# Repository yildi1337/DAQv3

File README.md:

# DAQv3
A Dual-Channel, Low Noise, Modular, 100 kHz Bandwidth, 24-Bit Data Acquisition (DAQ) Device / FFT Signal Analyzer

# Table of Contents

- **[Introduction](#introduction)**
- **[CAD Model](#cad-model)**
- **[Modules](#modules)**
  - [AnalogConversion_v1](#AnalogConversion_v1)
  - [AnalogConversion_v2](#AnalogConversion_v2)
  - [AnalogConversion_v3](#AnalogConversion_v3)
  - [Backplane_v1](#Backplane_v1)
  - [DigitalBackend_v1](#DigitalBackend_v1)
  - [PowerSupply_5V_v1](#PowerSupply_5V_v1)
  - [PowerSupply_5V_v2](#PowerSupply_5V_v2)
  - [PowerSupply_12V_v1](#PowerSupply_12V_v1)
  - [PowerSupply_12V_v2](#PowerSupply_12V_v2)
  - [USBConnectors_v1](#USBConnectors_v1)
- **[Firmware](#firmware)**
- **[USB Driver](#usb-driver)**
- **[Debug and Control Interface](#debug-and-control-interface)**
- **[Measurement Results](#measurement-results)**
  - [Linear Power Supply vs. Switched-Mode Power Supply](#linear-power-supply-vs-switched-mode-power-supply)
  - [Differential Input Module (AnalogConversion_v3)](#differential-input-module-analogconversion_v3)

# Introduction

Work in progress ...

# Rack
+ [Card Rail](https://it.rs-online.com/web/p/montanti-rack/2457848)
+ [Front Pannel Large](https://it.rs-online.com/web/p/accessori-per-contenitori/2879769) (10 HP)
+ [Front Pannel Small](https://us.rs-online.com/product/nvent-schroff/20848664/70294016/)  (4 HP)
+ [Case](https://it.rs-online.com/web/p/contenitori-e-scatole-rack/2550700?searchId=d65bfb2c-882b-444f-99ba-9c0d112e01d9&gb=s)  (42 HP)
+ [IEC Connector](https://it.rs-online.com/web/p/filtri-iec/8703669)

# CAD Model

The complete CAD model can be downloaded <a href="https://github.com/yildi1337/DAQv3/tree/main/cad_complete/inventor">here</a> (Autodesk Inventor 2023 files) including all <a href="#modules">modules</a> and the case.

# Modules

## AnalogConversion_v1

- [Schematics (PDF)](https://github.com/yildi1337/DAQv3/blob/main/schematics/AnalogConversion_v1_Schematics.pdf)
- [Schematics (Eagle)](https://github.com/yildi1337/DAQv3/blob/main/eagle/AnalogConversion_v1.sch)
- [Board (Eagle)](https://github.com/yildi1337/DAQv3/blob/main/eagle/AnalogConversion_v1.brd)
- [Gerber Files](https://github.com/yildi1337/DAQv3/blob/main/pcb_gerber/AnalogConversion_v1_2022-03-20.zip)
- [3D Step File](https://github.com/yildi1337/DAQv3/blob/main/cad_modules_step/AnalogConversion_v1.step)
- [Bill of Materials](https://github.com/yildi1337/DAQv3/blob/main/pcb_bom/BOM_AnalogConversion_v1.txt)

## AnalogConversion_v2

- [Schematics (PDF)](https://github.com/yildi1337/DAQv3/blob/main/schematics/AnalogConversion_v2_Schematics.pdf)
- [Schematics (Eagle)](https://github.com/yildi1337/DAQv3/blob/main/eagle/AnalogConversion_v2.sch)
- [Board (Eagle)](https://github.com/yildi1337/DAQv3/blob/main/eagle/AnalogConversion_v2.brd)
- [Gerber Files](https://github.com/yildi1337/DAQv3/blob/main/pcb_gerber/AnalogConversion_v2_2022-05-25.zip)
- [3D Step File](https://github.com/yildi1337/DAQv3/blob/main/cad_modules_step/AnalogConversion_v2.step)
- [Bill of Materials](https://github.com/yildi1337/DAQv3/blob/main/pcb_bom/BOM_AnalogConversion_v2.txt)

## AnalogConversion_v3

- [Schematics (PDF)](https://github.com/yildi1337/DAQv3/blob/main/schematics/AnalogConversion_v3_Schematics.pdf)
- [Schematics (Eagle)](https://github.com/yildi1337/DAQv3/blob/main/eagle/AnalogConversion_v3.sch)
- [Board (Eagle)](https://github.com/yildi1337/DAQv3/blob/main/eagle/AnalogConversion_v3.brd)
- [Gerber Files](https://github.com/yildi1337/DAQv3/blob/main/pcb_gerber/AnalogConversion_v3_2022-07-25.zip)
- [3D Step File](https://github.com/yildi1337/DAQv3/blob/main/cad_modules_step/AnalogConversion_v3.step)
- [Bill of Materials](https://github.com/yildi1337/DAQv3/blob/main/pcb_bom/BOM_AnalogConversion_v3.txt)

## Backplane_v1

- [Schematics (PDF)](https://github.com/yildi1337/DAQv3/blob/main/schematics/Backplane_v1_Schematics.pdf)
- [Schematics (Eagle)](https://github.com/yildi1337/DAQv3/blob/main/eagle/Backplane_v1.sch)
- [Board (Eagle)](https://github.com/yildi1337/DAQv3/blob/main/eagle/Backplane_v1.brd)
- [Gerber Files](https://github.com/yildi1337/DAQv3/blob/main/pcb_gerber/Backplane_v1_2022-03-20.zip)
- [3D Step File](https://github.com/yildi1337/DAQv3/blob/main/cad_modules_step/Backplane_v1.step)
- [Bill of Materials](https://github.com/yildi1337/DAQv3/blob/main/pcb_bom/BOM_Backplane_v1.txt)

## DigitalBackend_v1

- [Schematics (PDF)](https://github.com/yildi1337/DAQv3/blob/main/schematics/DigitalBackend_v1_Schematics.pdf)
- [Schematics (Eagle)](https://github.com/yildi1337/DAQv3/blob/main/eagle/DigitalBackend_v1.sch)
- [Board (Eagle)](https://github.com/yildi1337/DAQv3/blob/main/eagle/DigitalBackend_v1.brd)
- [Gerber Files](https://github.com/yildi1337/DAQv3/blob/main/pcb_gerber/DigitalBackend_v1_2022-03-20.zip)
- [3D Step File](https://github.com/yildi1337/DAQv3/blob/main/cad_modules_step/DigitalBackend_v1.step)
- [Bill of Materials](https://github.com/yildi1337/DAQv3/blob/main/pcb_bom/BOM_DigitalBackend_v1.txt)

## PowerSupply_12V_v1

- [Schematics (PDF)](https://github.com/yildi1337/DAQv3/blob/main/schematics/PowerSupply_12V_v1_Schematics.pdf)
- [Schematics (Eagle)](https://github.com/yildi1337/DAQv3/blob/main/eagle/PowerSupply_12V_v1.sch)
- [Board (Eagle)](https://github.com/yildi1337/DAQv3/blob/main/eagle/PowerSupply_12V_v1.brd)
- [Gerber Files](https://github.com/yildi1337/DAQv3/blob/main/pcb_gerber/PowerSupply_12V_v1_2022-03-20.zip)
- [3D Step File](https://github.com/yildi1337/DAQv3/blob/main/cad_modules_step/PowerSupply_12V_v1.step)
- [Bill of Materials](https://github.com/yildi1337/DAQv3/blob/main/pcb_bom/BOM_PowerSupply_12V_v1.txt)

## PowerSupply_12V_v2

- [Schematics (PDF)](https://github.com/yildi1337/DAQv3/blob/main/schematics/PowerSupply_12V_v2_Schematics.pdf)
- [Schematics (Eagle)](https://github.com/yildi1337/DAQv3/blob/main/eagle/PowerSupply_12V_v2.sch)
- [Board (Eagle)](https://github.com/yildi1337/DAQv3/blob/main/eagle/PowerSupply_12V_v2.brd)
- [Gerber Files](https://github.com/yildi1337/DAQv3/blob/main/pcb_gerber/PowerSupply_12V_v2_2022-05-25.zip)
- [3D Step File](https://github.com/yildi1337/DAQv3/blob/main/cad_modules_step/PowerSupply_12V_v2.step)
- [Bill of Materials](https://github.com/yildi1337/DAQv3/blob/main/pcb_bom/BOM_PowerSupply_12V_v2.txt)

## PowerSupply_5V_v1

- [Schematics (PDF)](https://github.com/yildi1337/DAQv3/blob/main/schematics/PowerSupply_5V_v1_Schematics.pdf)
- [Schematics (Eagle)](https://github.com/yildi1337/DAQv3/blob/main/eagle/PowerSupply_5V_v1.sch)
- [Board (Eagle)](https://github.com/yildi1337/DAQv3/blob/main/eagle/PowerSupply_5V_v1.brd)
- [Gerber Files](https://github.com/yildi1337/DAQv3/blob/main/pcb_gerber/PowerSupply_5V_v1_2022-03-20.zip)
- [3D Step File](https://github.com/yildi1337/DAQv3/blob/main/cad_modules_step/PowerSupply_5V_v1.step)
- [Bill of Materials](https://github.com/yildi1337/DAQv3/blob/main/pcb_bom/BOM_PowerSupply_5V_v1.txt)

## PowerSupply_5V_v2

- [Schematics (PDF)](https://github.com/yildi1337/DAQv3/blob/main/schematics/PowerSupply_5V_v2_Schematics.pdf)
- [Schematics (Eagle)](https://github.com/yildi1337/DAQv3/blob/main/eagle/PowerSupply_5V_v2.sch)
- [Board (Eagle)](https://github.com/yildi1337/DAQv3/blob/main/eagle/PowerSupply_5V_v2.brd)
- [Gerber Files](https://github.com/yildi1337/DAQv3/blob/main/pcb_gerber/PowerSupply_5V_v2_2022-05-25.zip)
- [3D Step File](https://github.com/yildi1337/DAQv3/blob/main/cad_modules_step/PowerSupply_5V_v2.step)
- [Bill of Materials](https://github.com/yildi1337/DAQv3/blob/main/pcb_bom/BOM_PowerSupply_5V_v2.txt)

## USBConnectors_v1

- [Schematics (PDF)](https://github.com/yildi1337/DAQv3/blob/main/schematics/USBConnectors_v1_Schematics.pdf)
- [Schematics (Eagle)](https://github.com/yildi1337/DAQv3/blob/main/eagle/USBConnectors_v1.sch)
- [Board (Eagle)](https://github.com/yildi1337/DAQv3/blob/main/eagle/USBConnectors_v1.brd)
- [Gerber Files](https://github.com/yildi1337/DAQv3/blob/main/pcb_gerber/USBConnectors_v1_2022-03-14.zip)
- [3D Step File](https://github.com/yildi1337/DAQv3/blob/main/cad_modules_step/USBConnectors_v1.step)
- [Bill of Materials](https://github.com/yildi1337/DAQv3/blob/main/pcb_bom/BOM_USBConnectors_v1.txt)

# Firmware

The firmware running on the STM32H753ZIT6 is mainly written in ANSI C and has been developed in <a href="https://www.st.com/en/development-tools/stm32cubeide.html">STM32CubeIDE</a> version 1.10.1 utilizing the official <a href="https://github.com/STMicroelectronics/stm32h7xx_hal_driver">STM32H7xx_HAL_Driver</a>. Among others, the firmware performs the following tasks:

- Configuration of the ADC AD7768 (on module <a href="#AnalogConversion_v3">AnalogConversion_v3</a>) via SPI (SPI_3).
- Reception of sampled data from the ADC AD7768 via SPI (SPI_2) and DMA (DMA1_Stream0).
- Transmission of sampled data from the ADC AD7768 via USB 2.0 Hi-Speed to the PC utilizing ULPI interface and an additional Hi-Speed USB PHY (USB3300).
- Handling USART connection (USART_1, via FT232RL chip on <a href="#USBConnectors_v1">USBConnectors_v1</a>) for debug purposes and for exchanging control/status commands with the PC.
- Controlling I2C bus (I2C_4) for controlling I/O expander TCA9534A (e.g. on module <a href="#AnalogConversion_v3">AnalogConversion_v3</a>) which, in turn, drives a relay driver (MAX4820) on the same module.
- Controlling front LEDs (on module <a href="#DigitalBackend_v1">DigitalBackend_v1</a>).

The complete source code can be found <a href="https://github.com/yildi1337/DAQv3/tree/main/firmware">here</a>.

# USB Driver

Two USB drivers are needed for operating the DAQ v3:

- For the reception of the sampled data from the ADC NI-VISA is utilized. The driver matching the hardware of this project has been generated with the NI-VISA Driver Wizard an can be downloaded <a href="https://github.com/yildi1337/DAQv3/tree/main/usb_driver/ni-visa">here</a>.
- To use the USB debug interface only the official USB serial driver from FTDI is required, which can be downloaded <a href="https://github.com/yildi1337/DAQv3/tree/main/usb_driver/ftdi">here</a>.

# Debug and Control Interface

Tool for graphical display of status information and for controlling the hardware via the virtual serial interface (second USB-B port). The python source code and a binary (only tested on x64 Microsoft Windows 10) can be downloaded <a href="https://github.com/yildi1337/DAQv3/tree/main/debug_interface">here</a>. 

# Measurement Results

## Linear Power Supply vs. Switched-Mode Power Supply

Noise measurements (60 seconds) were performed while powering the electronics with the power supplies of versions v1 and v2, where the abbreviations PS and ACNV in the titles refer to the power supply and analog conversion modules.

The two linear power supply modules of version v1 both operate with transformers. This resulted in heavy magnetic interference in the form of the mains frequency and multiples thereof.

The two power supply modules of version v2 both operate with AC/DC power modules (<a href="https://www.tracopower.com/de/deu/model/tmlm-20105">TMLM 20105</a>, <a href="https://www.tracopower.com/de/deu/model/tmlm-20115">TMLM 20115</a>) from Traco Power. Their switching frequencies are around 132 +/- 8 kHz and thus above the useful range of 0 - 100 kHz (Nyquist frequency is 128 kHz).

## Differential Input Module (AnalogConversion_v3)

The investigated setup consists of the modules:

- <a href="#Backplane_v1">Backplane_v1</a>
- <a href="#PowerSupply_5V_v2">PowerSupply_5V_v2</a>
- <a href="#PowerSupply_12V_v2">PowerSupply_12V_v2</a>
- <a href="#AnalogConversion_v3">AnalogConversion_v3</a>
- <a href="#DigitalBackend_v1">DigitalBackend_v1</a>
- <a href="#USBConnectors_v1">USBConnectors_v1</a>

### Mains Interference and Grounding

The two differential inputs of each channel were connected via <a href="https://www.mouser.de/ProductDetail/Amphenol-RF/132360?qs=V8V9vCxO5JtDrelx3RqrVA%3D%3D">50 Ohm SMA resistors</a> with AGND (SHIELD connected via R6 = 0 Ohm with AGND, <a href="https://github.com/yildi1337/DAQv3/blob/main/schematics/AnalogConversion_v3_Schematics.pdf">see schematics</a>).

Obviously, the lowest interference occurs in grounded mode and when GND of the backplane is directly connected to the chassis/the protective earth connector of the power entry module (first plot).

### Input Noise of Differential Opamp Driver and ADC

The measurement result from above is essential for the further development of the preamplifier. The gain of the preamplifier must be high enough to be able to neglect the noise from the opamp driver (ADA4945-1) and ADC (AD7768-4) determined here. A useful model for describing the power spectral density of the voltage noise $PSD(f)$ (in units of $\mathrm{V}^2/\mathrm{Hz}$) is the polynomial law 
$$\mathrm{PSD}(f) = \mathrm{LSD}^2(f) = \sum_{i=-1}^{0} b_i f^i$$ 
where $i=0$ and $i=-1$ refer to white noise and $1/f$ flicker noise, respectively, and $\mathrm{LSD}(f)$ referes to the linear spectrum density (in units of $\mathrm{V}/\sqrt{\mathrm{Hz}}$). For this measurement, values of
- $b_{-1} = 1.3 \cdot 10^{-13}~\mathrm{V}^2$
- $b_0 = {1.3 \cdot 10^{-15}~\mathrm{V}^2/\mathrm{Hz}}$
were found.

This results in a $1/f$ corner frequency of $f_{\mathrm{c}} = b_{-1}/b_0 = 100~\mathrm{Hz}$. The white voltage noise density is equal to $\sqrt{b_0} = 36~\mathrm{nV}/\sqrt{\mathrm{Hz}}$. Based on the two time domain noise signals RMS noise values of $13.2~\mu\mathrm{V}$ (channel 1) and $13.5~\mu\mathrm{V}$ (channel 2) were determined after substracting the DC offsets of $-6.5~\mathrm{mV}$ and $-1.8~\mathrm{mV}$.

The measured RMS noise values are in good agreement with the value of $11.58~\mu\mathrm{V}$ given in the datasheet (for the ADC only).

In addition, for $V_{\mathrm{ref}} = 5~\mathrm{V}$, the dynamic range of the utilized combination of opamp driver and ADC is better than 

$$\mathrm{DR} = 20 \cdot \log_{10}\left(\frac{2 \cdot V_{\mathrm{ref}}}{\sqrt{2} \cdot \mathrm{RMS}\ \mathrm{noise}}\right)~\mathrm{dB} = 114\ \mathrm{dB}$$ 

### ADC RAW Data for Several Input Configurations

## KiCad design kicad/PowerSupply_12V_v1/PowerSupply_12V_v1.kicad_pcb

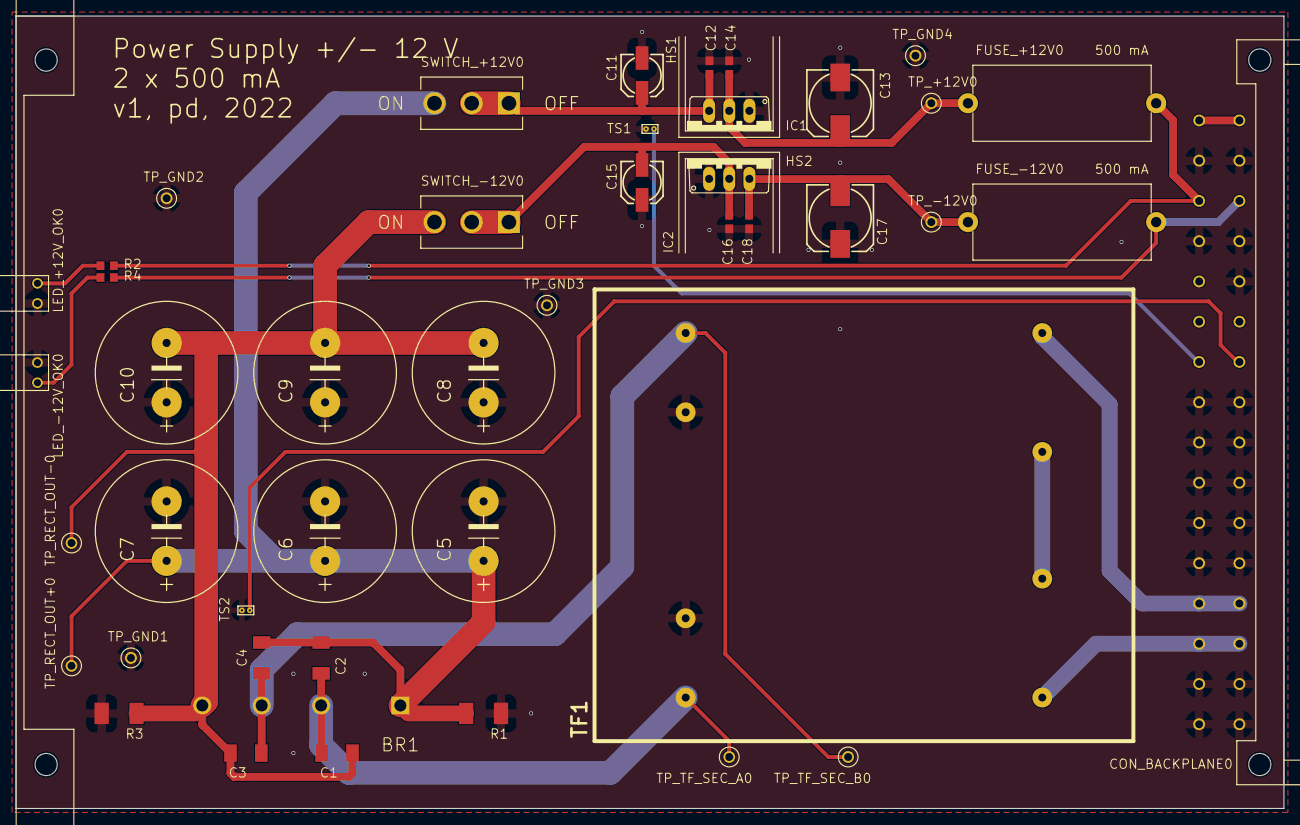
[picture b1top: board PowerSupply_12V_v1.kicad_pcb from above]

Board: 2 copper layers, 160.0 x 100.0 mm, 48 parts (0 on the bottom side), 19 nets.

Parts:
BR1: GBJ610; GBJ610_24264370
C1, C2, C3, C4: 10n/1kV; C1808_18640681
C5, C6, C7, C8, C9, C10: 10000u/25V; EEUHD1E103_33731490
C11, C15: 22u/25V; 153CLV-0505_18640681
C12, C14, C16, C18: 100n; C0603_18640681
C13, C17: 100u/25V; 153CLV-0810_18640681
CON_BACKPLANE0: 09031326921; 09031326921_33573412
FUSE_+12V0: 0031.8201; 0031.8201_24323731
FUSE_-12V0: 0031.8201; 0031.8201_24323731
HS1, HS2: FK 237 SA 220 O; FK_237_SA_220_O_33584193
IC1: LM1085IT-12; LM1085IT-12_33765943
IC2: LM2990T-12; LM2990T-12_33765966
LED_+12V_OK0: 113-314-04; 113-314-04_33630242
LED_-12V_OK0: 113-314-04; 113-314-04_33630242
PCB_BRACKET0: 60807-011; 60807-011_33573280
R1, R3: 360/2W; R2010_18640681
R2, R4: 680; R0603_18640681
SWITCH_+12V0: RSPRO-SPDT-SLIDE-SWITCH-7347334; RSPRO-SPDT-SLIDE-SWITCH-7347334_23627966
SWITCH_-12V0: RSPRO-SPDT-SLIDE-SWITCH-7347334; RSPRO-SPDT-SLIDE-SWITCH-7347334_23627966
TF1: FL 24/12; FL_24-12_33729599
TP_+12V0: RSPRO-1MM-TERMINAL-POST-2622034_23908750
TP_-12V0: RSPRO-1MM-TERMINAL-POST-2622034_23908750
TP_GND1, TP_GND2, TP_GND3, TP_GND4: RSPRO-1MM-TERMINAL-POST-2622034_23908750
TP_RECT_OUT+0: RSPRO-1MM-TERMINAL-POST-2622034_23908750
TP_RECT_OUT-0: RSPRO-1MM-TERMINAL-POST-2622034_23908750
TP_TF_SEC_A0: RSPRO-1MM-TERMINAL-POST-2622034_23908750
TP_TF_SEC_B0: RSPRO-1MM-TERMINAL-POST-2622034_23908750
TS1, TS2: NB-PTCO-160; NB-PTCO-160_24346792

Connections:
+5V: CON_BACKPLANE0.1, CON_BACKPLANE0.2
+12V: CON_BACKPLANE0.5, FUSE_+12V0.2, R2.2
-12V: CON_BACKPLANE0.6, FUSE_-12V0.2, R4.1
BITE_PS_12V_TS1: CON_BACKPLANE0.13, TS1.1
BITE_PS_12V_TS2: CON_BACKPLANE0.14, TS2.1
GND: C5.-, C6.-, C7.-, C8.+, C9.+, C10.+, C11.-, C12.2, C13.-, C14.2, C15.+, C16.1, C17.+, C18.1, CON_BACKPLANE0.3, CON_BACKPLANE0.4, CON_BACKPLANE0.7, CON_BACKPLANE0.8, CON_BACKPLANE0.10, CON_BACKPLANE0.15, CON_BACKPLANE0.16, CON_BACKPLANE0.17, CON_BACKPLANE0.18, CON_BACKPLANE0.19, CON_BACKPLANE0.20, CON_BACKPLANE0.21, CON_BACKPLANE0.22, CON_BACKPLANE0.23, CON_BACKPLANE0.24, CON_BACKPLANE0.29, CON_BACKPLANE0.30, CON_BACKPLANE0.31, CON_BACKPLANE0.32, IC1.1, IC2.1, LED_+12V_OK0.-, LED_-12V_OK0.+, R1.1, R3.2, TF1.S1B, TF1.S2A, TP_GND1.P$1, TP_GND2.P$1, TP_GND3.P$1, TP_GND4.P$1, TS1.2, TS2.2
L: CON_BACKPLANE0.27, CON_BACKPLANE0.28, TF1.P1A
N: CON_BACKPLANE0.25, CON_BACKPLANE0.26, TF1.P2B
unnamed: C15.-, C16.2, IC2.2, SWITCH_-12V0.1, SWITCH_-12V0.2
unnamed: LED_-12V_OK0.-, R4.2
unnamed: C17.-, C18.2, FUSE_-12V0.1, IC2.3, TP_-12V0.P$1
unnamed: TF1.P1B, TF1.P2A
unnamed: BR1.L, C1.1, C2.1, TF1.S1A, TP_TF_SEC_A0.P$1
unnamed: LED_+12V_OK0.+, R2.1
unnamed: C13.+, C14.1, FUSE_+12V0.1, IC1.2, TP_+12V0.P$1
unnamed: BR1.N, C3.2, C4.2, TF1.S2B, TP_TF_SEC_B0.P$1
unnamed: C11.+, C12.1, IC1.3, SWITCH_+12V0.1, SWITCH_+12V0.2
RECT_OUT+: BR1.+, C2.2, C4.1, C5.+, C6.+, C7.+, R1.2, SWITCH_+12V0.3, TP_RECT_OUT+0.P$1
RECT_OUT-: BR1.-, C1.2, C3.1, C8.-, C9.-, C10.-, R3.1, SWITCH_-12V0.3, TP_RECT_OUT-0.P$1

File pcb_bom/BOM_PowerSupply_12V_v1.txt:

Qty Value                           Device                          Package                         Parts                                                                                                      Description                          POPULARITY SPICEPREFIX
10                                  RSPRO-1MM-TERMINAL-POST-2622034 RSPRO-1MM-TERMINAL-POST-2622034 TP_+12V, TP_-12V, TP_GND1, TP_GND2, TP_GND3, TP_GND4, TP_RECT_OUT+, TP_RECT_OUT-, TP_TF_SEC_A, TP_TF_SEC_B                                                            
2   0031.8201                       0031.8201                       0031.8201                       FUSE_+12V, FUSE_-12V                                                                                                                                                  
1   09031326921                     09031326921                     09031326921                     CON_BACKPLANE                                                                                                                                                         
6   10000u/25V                      EEUHD1E103                      EEUHD1E103                      C5, C6, C7, C8, C9, C10                                                                                                                                               
4   100n                            C-EUC0603                       C0603                           C12, C14, C16, C18                                                                                         CAPACITOR, European symbol           73         C          
2   100u/25V                        CPOL-EU153CLV-0810              153CLV-0810                     C13, C17                                                                                                   POLARIZED CAPACITOR, European symbol 4          C          
4   10n/1kV                         C-EUC1808                       C1808                           C1, C2, C3, C4                                                                                             CAPACITOR, European symbol           0          C          
2   113-314-04                      113-314-04                      113-314-04                      LED_+12V_OK, LED_-12V_OK                                                                                                                                              
2   22u/25V                         CPOL-EU153CLV-0505              153CLV-0505                     C11, C15                                                                                                   POLARIZED CAPACITOR, European symbol 3          C          
2   360/2W                          R-EU_R2010                      R2010                           R1, R3                                                                                                     RESISTOR, European symbol            3          R          
1   60807-011                       60807-011                       60807-011                       PCB_BRACKET                                                                                                                                                           
2   680                             R-EU_R0603                      R0603                           R2, R4                                                                                                     RESISTOR, European symbol            70         R          
2   FK 237 SA 220 O                 FK_237_SA_220_O                 FK_237_SA_220_O                 HS1, HS2                                                                                                                                                              
1   FL 24/12                        FL_24-12                        FL_24-12                        TF1                                                                                                                                                                   
1   GBJ610                          GBJ610                          GBJ610                          BR1                                                                                                                                                                   
1   LM1085IT-12                     LM1085IT-12                     LM1085IT-12                     IC1                                                                                                                                                                   
1   LM2990T-12                      LM2990T-12                      LM2990T-12                      IC2                                                                                                                                                                   
2   NB-PTCO-160                     NB-PTCO-160                     NB-PTCO-160                     TS1, TS2                                                                                                                                                              
2   RSPRO-SPDT-SLIDE-SWITCH-7347334 RSPRO-SPDT-SLIDE-SWITCH-7347334 RSPRO-SPDT-SLIDE-SWITCH-7347334 SWITCH_+12V, SWITCH_-12V

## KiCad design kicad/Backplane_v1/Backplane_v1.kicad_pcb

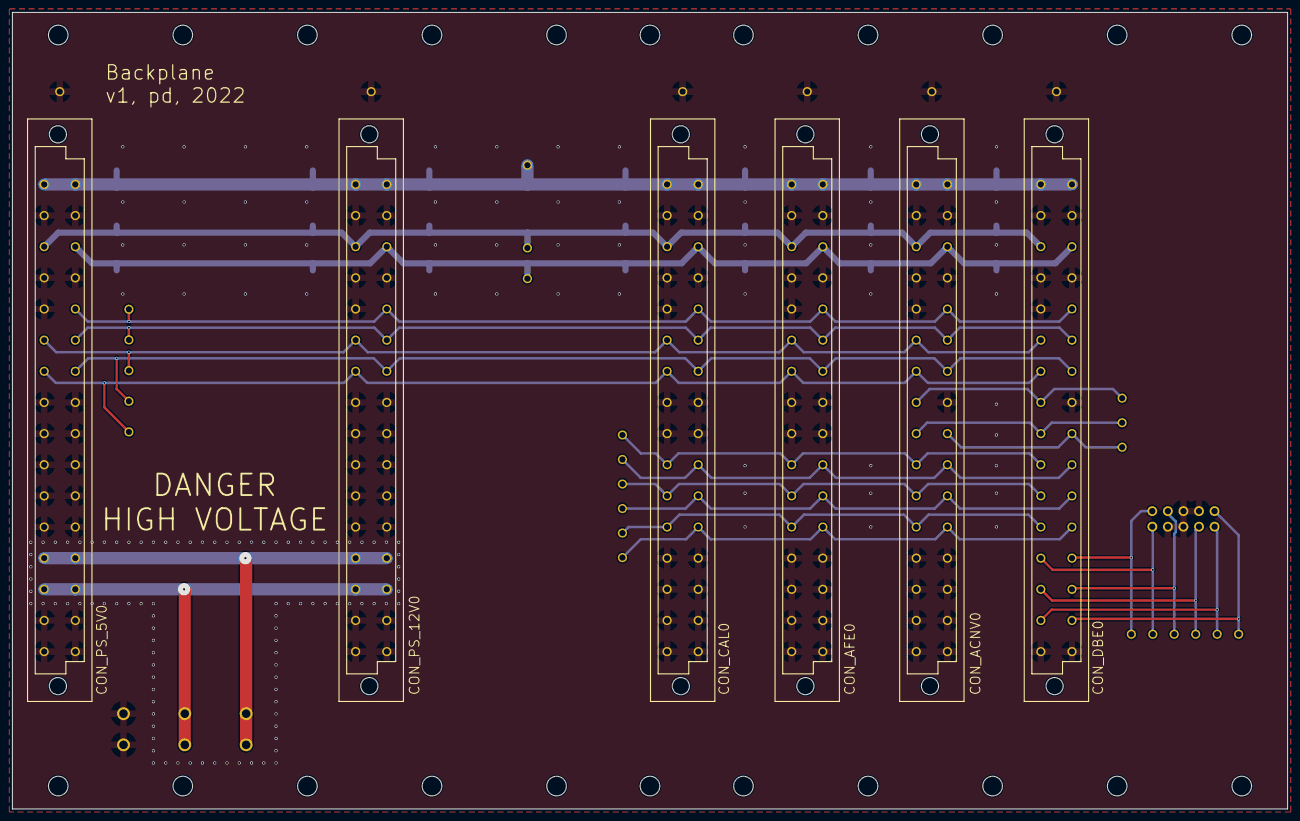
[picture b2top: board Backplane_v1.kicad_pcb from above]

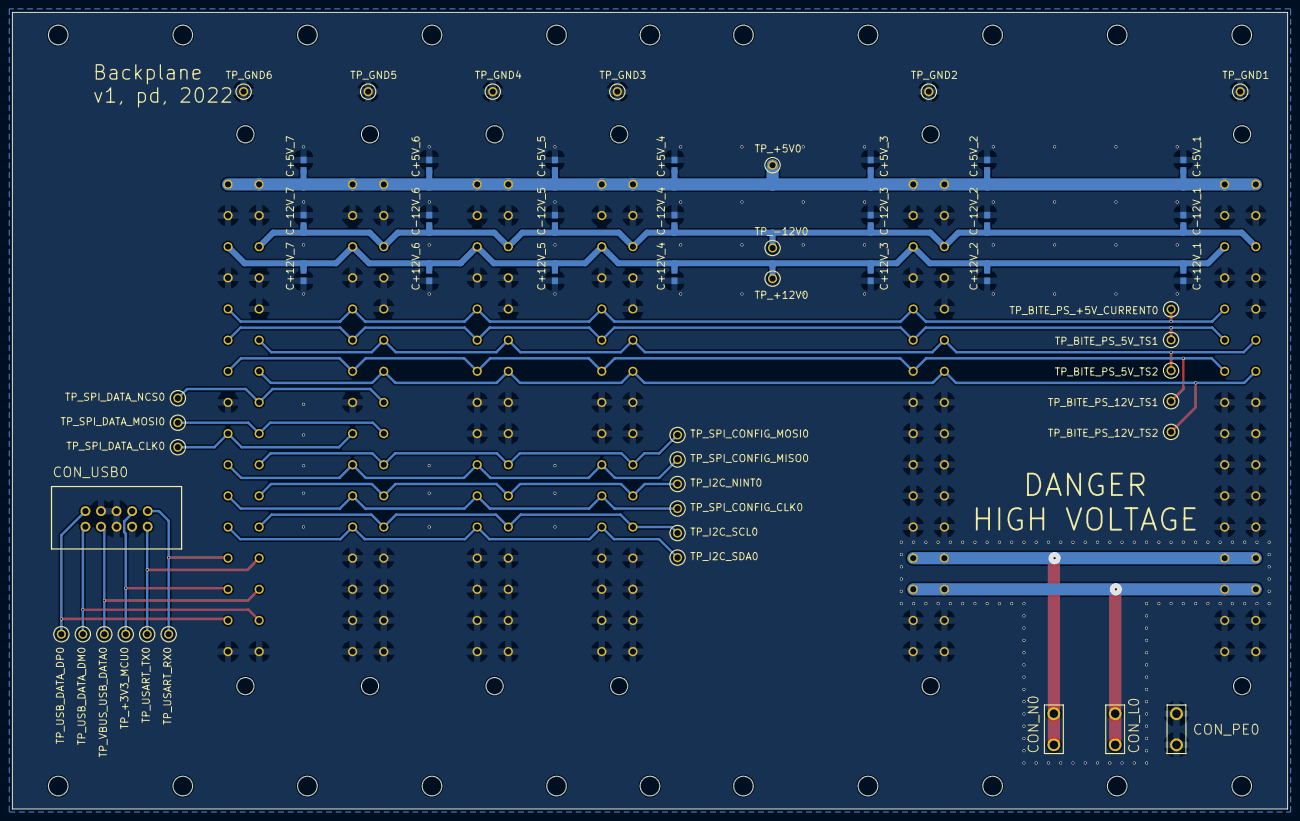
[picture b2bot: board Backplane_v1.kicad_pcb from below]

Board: 2 copper layers, 208.0 x 129.9 mm, 82 parts (54 on the bottom side), 26 nets.

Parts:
C+5V_1, C+5V_2, C+5V_3, C+5V_4, C+5V_5, C+5V_6, C+5V_7, C+12V_1, C+12V_2, C+12V_3, C+12V_4, C+12V_5, C+12V_6, C+12V_7: 100n; C0603_18640681
C-12V_1, C-12V_2, C-12V_3, C-12V_4, C-12V_5, C-12V_6, C-12V_7: 100n; C0603_18640681
CON_ACNV0: 09032326825; 09032326825_33780477
CON_AFE0: 09032326825; 09032326825_33780477
CON_CAL0: 09032326825; 09032326825_33780477
CON_DBE0: 09032326825; 09032326825_33780477
CON_L0: 63824-1; 63824-1_24300571
CON_N0: 63824-1; 63824-1_24300571
CON_PE0: 63824-1; 63824-1_24300571
CON_PS_5V0, CON_PS_12V0: 09032326825; 09032326825_33780477
CON_USB0: TST-105-01-T-D; TST-105-01-T-D_27603653
TP_+3V3_MCU0, TP_+5V0, TP_+12V0: RSPRO-1MM-TERMINAL-POST-2622034_23908750
TP_-12V0: RSPRO-1MM-TERMINAL-POST-2622034_23908750
TP_BITE_PS_5V_TS1, TP_BITE_PS_5V_TS2, TP_BITE_PS_12V_TS1, TP_BITE_PS_12V_TS2: RSPRO-1MM-TERMINAL-POST-2622034_23908750
TP_BITE_PS_+5V_CURRENT0: RSPRO-1MM-TERMINAL-POST-2622034_23908750
TP_GND1, TP_GND2, TP_GND3, TP_GND4, TP_GND5, TP_GND6: RSPRO-1MM-TERMINAL-POST-2622034_23908750
TP_I2C_NINT0, TP_I2C_SCL0, TP_I2C_SDA0: RSPRO-1MM-TERMINAL-POST-2622034_23908750
TP_SPI_CONFIG_CLK0: RSPRO-1MM-TERMINAL-POST-2622034_23908750
TP_SPI_CONFIG_MISO0: RSPRO-1MM-TERMINAL-POST-2622034_23908750
TP_SPI_CONFIG_MOSI0: RSPRO-1MM-TERMINAL-POST-2622034_23908750
TP_SPI_DATA_CLK0: RSPRO-1MM-TERMINAL-POST-2622034_23908750
TP_SPI_DATA_MOSI0: RSPRO-1MM-TERMINAL-POST-2622034_23908750
TP_SPI_DATA_NCS0: RSPRO-1MM-TERMINAL-POST-2622034_23908750
TP_USART_RX0: RSPRO-1MM-TERMINAL-POST-2622034_23908750
TP_USART_TX0: RSPRO-1MM-TERMINAL-POST-2622034_23908750
TP_USB_DATA_DM0: RSPRO-1MM-TERMINAL-POST-2622034_23908750
TP_USB_DATA_DP0: RSPRO-1MM-TERMINAL-POST-2622034_23908750
TP_VBUS_USB_DATA0: RSPRO-1MM-TERMINAL-POST-2622034_23908750
UNK_HOLE_0: dummyfp0
UNK_HOLE_1: dummyfp1
UNK_HOLE_2: dummyfp2
UNK_HOLE_3: dummyfp3
UNK_HOLE_4: dummyfp4
UNK_HOLE_5: dummyfp5
UNK_HOLE_6: dummyfp6
UNK_HOLE_7: dummyfp7
UNK_HOLE_8: dummyfp8
UNK_HOLE_9: dummyfp9
UNK_HOLE_10: dummyfp10
UNK_HOLE_11: dummyfp11
UNK_HOLE_12: dummyfp12
UNK_HOLE_13: dummyfp13
UNK_HOLE_14: dummyfp14
UNK_HOLE_15: dummyfp15
UNK_HOLE_16: dummyfp16
UNK_HOLE_17: dummyfp17
UNK_HOLE_18: dummyfp18
UNK_HOLE_19: dummyfp19
UNK_HOLE_20: dummyfp20
UNK_HOLE_21: dummyfp21

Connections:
+3V3_MCU: CON_DBE0.27, CON_USB0.8, TP_+3V3_MCU0.P$1
+5V: C+5V_1.1, C+5V_2.1, C+5V_3.1, C+5V_4.1, C+5V_5.1, C+5V_6.1, C+5V_7.1, CON_ACNV0.1, CON_ACNV0.2, CON_AFE0.1, CON_AFE0.2, CON_CAL0.1, CON_CAL0.2, CON_DBE0.1, CON_DBE0.2, CON_PS_5V0.1, CON_PS_5V0.2, CON_PS_12V0.1, CON_PS_12V0.2, TP_+5V0.P$1
+12V: C+12V_1.1, C+12V_2.1, C+12V_3.1, C+12V_4.1, C+12V_5.1, C+12V_6.1, C+12V_7.1, CON_ACNV0.5, CON_AFE0.5, CON_CAL0.5, CON_DBE0.5, CON_PS_5V0.5, CON_PS_12V0.5, TP_+12V0.P$1
-12V: C-12V_1.1, C-12V_2.1, C-12V_3.1, C-12V_4.1, C-12V_5.1, C-12V_6.1, C-12V_7.1, CON_ACNV0.6, CON_AFE0.6, CON_CAL0.6, CON_DBE0.6, CON_PS_5V0.6, CON_PS_12V0.6, TP_-12V0.P$1
BITE_PS_5V_TS1: CON_ACNV0.11, CON_AFE0.11, CON_CAL0.11, CON_DBE0.11, CON_PS_5V0.11, CON_PS_12V0.11, TP_BITE_PS_5V_TS1.P$1
BITE_PS_5V_TS2: CON_ACNV0.12, CON_AFE0.12, CON_CAL0.12, CON_DBE0.12, CON_PS_5V0.12, CON_PS_12V0.12, TP_BITE_PS_5V_TS2.P$1
BITE_PS_12V_TS1: CON_ACNV0.13, CON_AFE0.13, CON_CAL0.13, CON_DBE0.13, CON_PS_5V0.13, CON_PS_12V0.13, TP_BITE_PS_12V_TS1.P$1
BITE_PS_12V_TS2: CON_ACNV0.14, CON_AFE0.14, CON_CAL0.14, CON_DBE0.14, CON_PS_5V0.14, CON_PS_12V0.14, TP_BITE_PS_12V_TS2.P$1
BITE_PS_+5V_CURRENT: CON_ACNV0.9, CON_AFE0.9, CON_CAL0.9, CON_DBE0.9, CON_PS_5V0.9, CON_PS_12V0.9, TP_BITE_PS_+5V_CURRENT0.P$1
GND: C+5V_1.2, C+5V_2.2, C+5V_3.2, C+5V_4.2, C+5V_5.2, C+5V_6.2, C+5V_7.2, C+12V_1.2, C+12V_2.2, C+12V_3.2, C+12V_4.2, C+12V_5.2, C+12V_6.2, C+12V_7.2, C-12V_1.2, C-12V_2.2, C-12V_3.2, C-12V_4.2, C-12V_5.2, C-12V_6.2, C-12V_7.2, CON_ACNV0.3, CON_ACNV0.4, CON_ACNV0.7, CON_ACNV0.8, CON_ACNV0.10, CON_ACNV0.15, CON_ACNV0.25, CON_ACNV0.26, CON_ACNV0.27, CON_ACNV0.28, CON_ACNV0.29, CON_ACNV0.30, CON_ACNV0.31, CON_ACNV0.32, CON_AFE0.3, CON_AFE0.4, CON_AFE0.7, CON_AFE0.8, CON_AFE0.10, CON_AFE0.15, CON_AFE0.16, CON_AFE0.17, CON_AFE0.18, CON_AFE0.25, CON_AFE0.26, CON_AFE0.27, CON_AFE0.28, CON_AFE0.29, CON_AFE0.30, CON_AFE0.31, CON_AFE0.32, CON_CAL0.3, CON_CAL0.4, CON_CAL0.7, CON_CAL0.8, CON_CAL0.10, CON_CAL0.15, CON_CAL0.16, CON_CAL0.17, CON_CAL0.18, CON_CAL0.25, CON_CAL0.26, CON_CAL0.27, CON_CAL0.28, CON_CAL0.29, CON_CAL0.30, CON_CAL0.31, CON_CAL0.32, CON_DBE0.3, CON_DBE0.4, CON_DBE0.7, CON_DBE0.8, CON_DBE0.10, CON_DBE0.15, CON_DBE0.31, CON_DBE0.32, CON_PE0.1, CON_PE0.2, CON_PS_5V0.3, CON_PS_5V0.4, CON_PS_5V0.7, CON_PS_5V0.8, CON_PS_5V0.10, CON_PS_5V0.15, CON_PS_5V0.16, CON_PS_5V0.17, CON_PS_5V0.18, CON_PS_5V0.19, CON_PS_5V0.20, CON_PS_5V0.21, CON_PS_5V0.22, CON_PS_5V0.23, CON_PS_5V0.24, CON_PS_5V0.29, CON_PS_5V0.30, CON_PS_5V0.31, CON_PS_5V0.32, CON_PS_12V0.3, CON_PS_12V0.4, CON_PS_12V0.7, CON_PS_12V0.8, CON_PS_12V0.10, CON_PS_12V0.15, CON_PS_12V0.16, CON_PS_12V0.17, CON_PS_12V0.18, CON_PS_12V0.19, CON_PS_12V0.20, CON_PS_12V0.21, CON_PS_12V0.22, CON_PS_12V0.23, CON_PS_12V0.24, CON_PS_12V0.29, CON_PS_12V0.30, CON_PS_12V0.31, CON_PS_12V0.32, CON_USB0.4, CON_USB0.5, CON_USB0.6, CON_USB0.7, TP_GND1.P$1, TP_GND2.P$1, TP_GND3.P$1, TP_GND4.P$1, TP_GND5.P$1, TP_GND6.P$1
I2C_NINT: CON_ACNV0.22, CON_AFE0.22, CON_CAL0.22, CON_DBE0.22, TP_I2C_NINT0.P$1
I2C_SCL: CON_ACNV0.24, CON_AFE0.24, CON_CAL0.24, CON_DBE0.24, TP_I2C_SCL0.P$1
I2C_SDA: CON_ACNV0.23, CON_AFE0.23, CON_CAL0.23, CON_DBE0.23, TP_I2C_SDA0.P$1
L: CON_L0.1, CON_L0.2, CON_PS_5V0.27, CON_PS_5V0.28, CON_PS_12V0.27, CON_PS_12V0.28
N: CON_N0.1, CON_N0.2, CON_PS_5V0.25, CON_PS_5V0.26, CON_PS_12V0.25, CON_PS_12V0.26
SPI_CONFIG_CLK: CON_ACNV0.21, CON_AFE0.21, CON_CAL0.21, CON_DBE0.21, TP_SPI_CONFIG_CLK0.P$1
SPI_CONFIG_MISO: CON_ACNV0.19, CON_AFE0.19, CON_CAL0.19, CON_DBE0.19, TP_SPI_CONFIG_MISO0.P$1
SPI_CONFIG_MOSI: CON_ACNV0.20, CON_AFE0.20, CON_CAL0.20, CON_DBE0.20, TP_SPI_CONFIG_MOSI0.P$1
SPI_DATA_CLK: CON_ACNV0.17, CON_DBE0.17, TP_SPI_DATA_CLK0.P$1
SPI_DATA_MOSI: CON_ACNV0.18, CON_DBE0.18, TP_SPI_DATA_MOSI0.P$1
SPI_DATA_NCS: CON_ACNV0.16, CON_DBE0.16, TP_SPI_DATA_NCS0.P$1
USART_RX: CON_DBE0.25, CON_USB0.10, TP_USART_RX0.P$1
USART_TX: CON_DBE0.26, CON_USB0.9, TP_USART_TX0.P$1
USB_DATA_DM: CON_DBE0.30, CON_USB0.1, TP_USB_DATA_DM0.P$1
USB_DATA_DP: CON_DBE0.29, CON_USB0.2, TP_USB_DATA_DP0.P$1
VBUS_USB_DATA: CON_DBE0.28, CON_USB0.3, TP_VBUS_USB_DATA0.P$1

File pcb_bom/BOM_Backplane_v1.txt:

Qty Value          Device                          Package                         Parts                                                                                                                                                                                                                                                                                                                                                                                                                             Description                POPULARITY SPICEPREFIX
29                 RSPRO-1MM-TERMINAL-POST-2622034 RSPRO-1MM-TERMINAL-POST-2622034 TP_+3V3_MCU, TP_+5V, TP_+12V, TP_-12V, TP_BITE_PS_+5V_CURRENT, TP_BITE_PS_5V_TS1, TP_BITE_PS_5V_TS2, TP_BITE_PS_12V_TS1, TP_BITE_PS_12V_TS2, TP_GND1, TP_GND2, TP_GND3, TP_GND4, TP_GND5, TP_GND6, TP_I2C_NINT, TP_I2C_SCL, TP_I2C_SDA, TP_SPI_CONFIG_CLK, TP_SPI_CONFIG_MISO, TP_SPI_CONFIG_MOSI, TP_SPI_DATA_CLK, TP_SPI_DATA_MOSI, TP_SPI_DATA_NCS, TP_USART_RX, TP_USART_TX, TP_USB_DATA_DM, TP_USB_DATA_DP, TP_VBUS_USB_DATA                                                  
6   09032326825    09032326825                     09032326825                     CON_ACNV, CON_AFE, CON_CAL, CON_DBE, CON_PS_5V, CON_PS_12V                                                                                                                                                                                                                                                                                                                                                                                                                         
21  100n           C-EUC0603                       C0603                           C+5V_1, C+5V_2, C+5V_3, C+5V_4, C+5V_5, C+5V_6, C+5V_7, C+12V_1, C+12V_2, C+12V_3, C+12V_4, C+12V_5, C+12V_6, C+12V_7, C-12V_1, C-12V_2, C-12V_3, C-12V_4, C-12V_5, C-12V_6, C-12V_7                                                                                                                                                                                                                                              CAPACITOR, European symbol 73         C          
3   63824-1        63824-1                         63824-1                         CON_L, CON_N, CON_PE                                                                                                                                                                                                                                                                                                                                                                                                                                                               
1   TST-105-01-T-D TST-105-01-T-D                  TST-105-01-T-D                  CON_USB
